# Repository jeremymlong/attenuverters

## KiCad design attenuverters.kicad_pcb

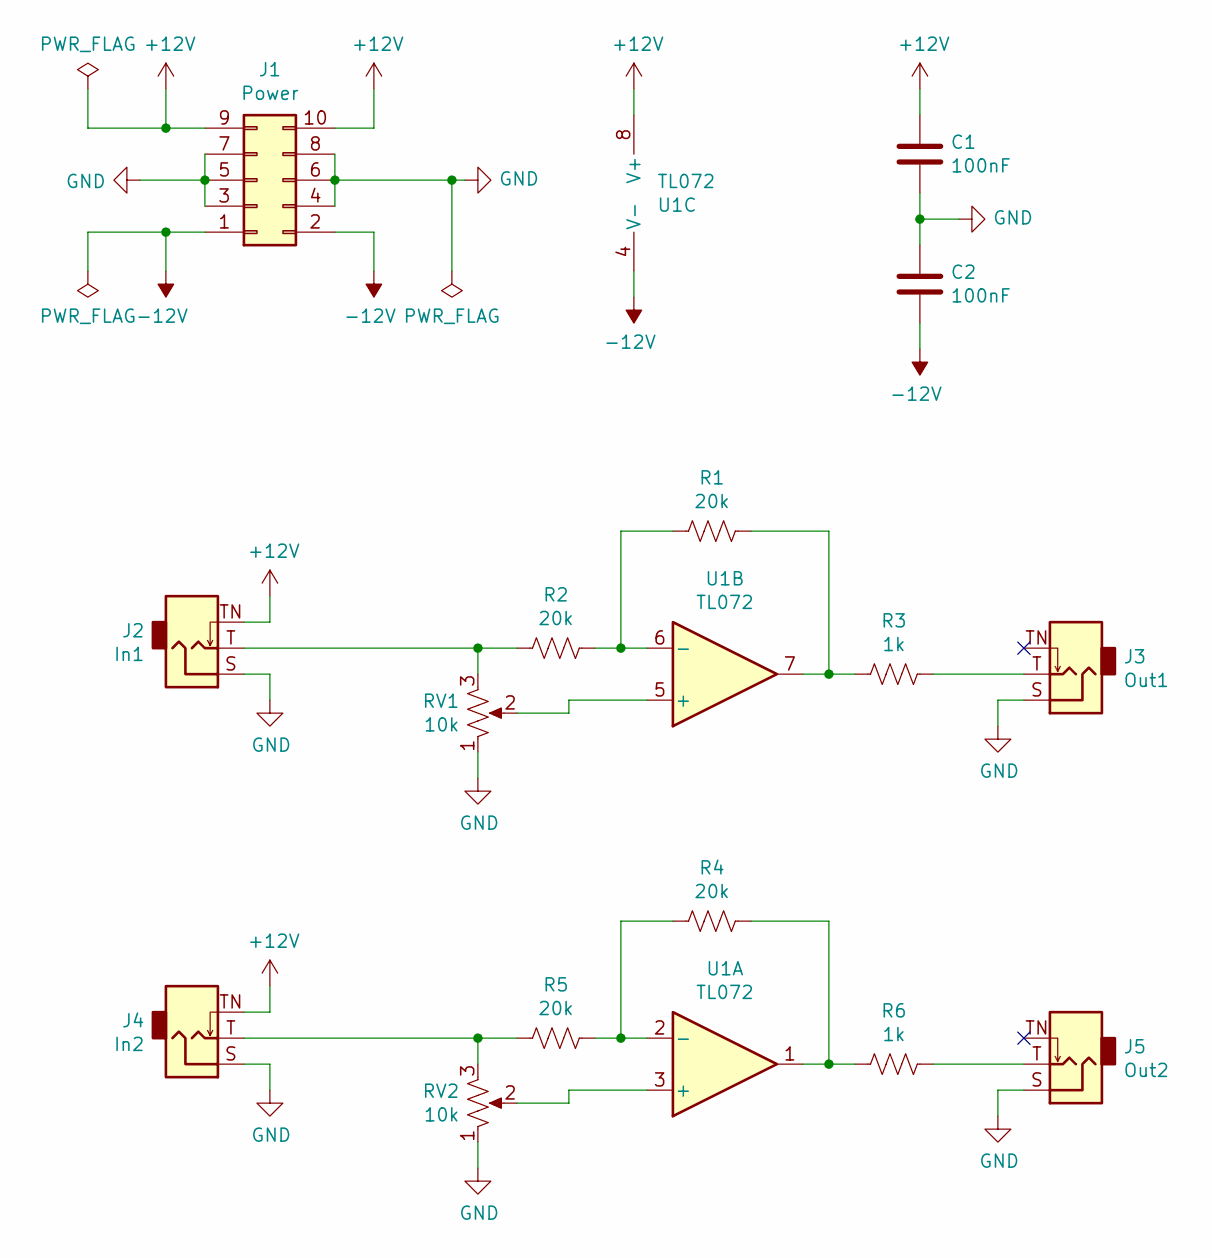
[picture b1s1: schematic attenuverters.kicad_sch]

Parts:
C1, C2: 100nF; C_0805_2012Metric_Pad1.18x1.45mm_HandSolder
J1: Power; IDC-Header_2x05_P2.54mm_Vertical
J2: In1; Jack_3.5mm_QingPu_WQP-PJ398SM_Vertical_CircularHoles
J3: Out1; Jack_3.5mm_QingPu_WQP-PJ398SM_Vertical_CircularHoles
J4: In2; Jack_3.5mm_QingPu_WQP-PJ398SM_Vertical_CircularHoles
J5: Out2; Jack_3.5mm_QingPu_WQP-PJ398SM_Vertical_CircularHoles
R1, R2, R4, R5: 20k; R_0805_2012Metric_Pad1.20x1.40mm_HandSolder
R3, R6: 1k; R_0805_2012Metric_Pad1.20x1.40mm_HandSolder
RV1, RV2: 10k; Potentiometer_Alpha_RD901F-40-00D_Single_Vertical_CircularH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
U1: TL072; SOIC-8_3.9x4.9mm_P1.27mm

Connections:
+12V: C1.1, J1.9, J1.10, J2.TN, J4.TN, U1.8 (V+)
-12V: C2.2, J1.1, J1.2, U1.4 (V-)
GND: C1.2, C2.1, J1.3, J1.4, J1.5, J1.6, J1.7, J1.8, J2.S, J3.S, J4.S, J5.S, RV1.1, RV2.1
unnamed: J2.T, R2.2, RV1.3
unnamed: J3.T, R3.1
unnamed: J4.T, R5.2, RV2.3
unnamed: J5.T, R6.1
unnamed: R1.1, R3.2, U1.7
unnamed: R4.1, R6.2, U1.1
unnamed: RV2.2, U1.3 (+)
unnamed: R4.2, R5.1, U1.2 (-)
unnamed: RV1.2, U1.5 (+)
unnamed: R1.2, R2.1, U1.6 (-)

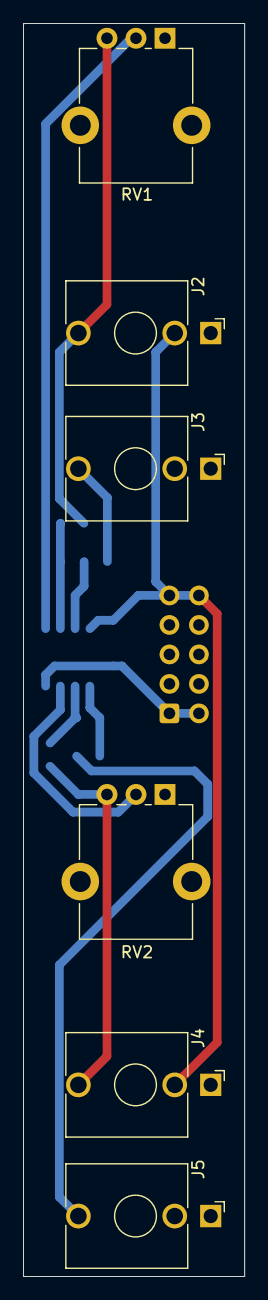
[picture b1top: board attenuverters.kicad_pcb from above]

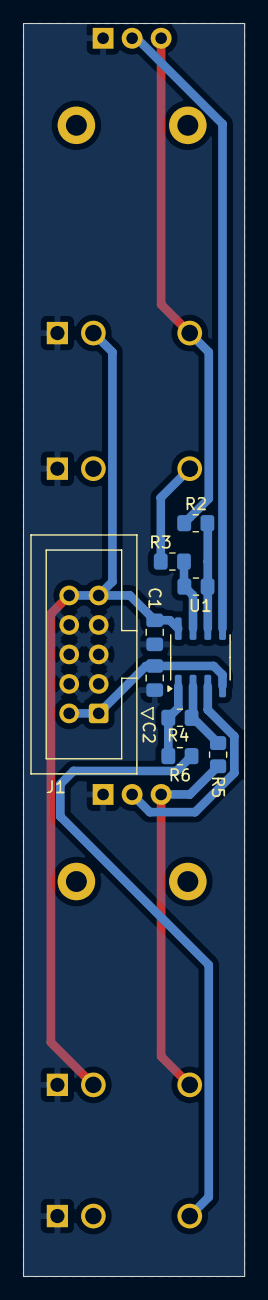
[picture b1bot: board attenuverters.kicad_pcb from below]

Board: 2 copper layers, 19.0 x 107.9 mm, 16 parts (10 on the bottom side), 13 nets.

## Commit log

2024-03-25 Create LICENSE
2024-04-08 Fixed power, updated KiCAD version
